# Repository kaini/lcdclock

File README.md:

# 7-Segment LCD Clock

Schematic, PCB and firmware (C++) for a 7-segment LCD clock. For details please
see [my site](https://me.pushrax.com/lcd-clock/).

## Build Instructions

Just use `make`. If you want a release build use `make RELEASE=1`. If you
have a SEGGER J-Link you can use `make flash` to flash the build output
onto a compatible microcontroller.

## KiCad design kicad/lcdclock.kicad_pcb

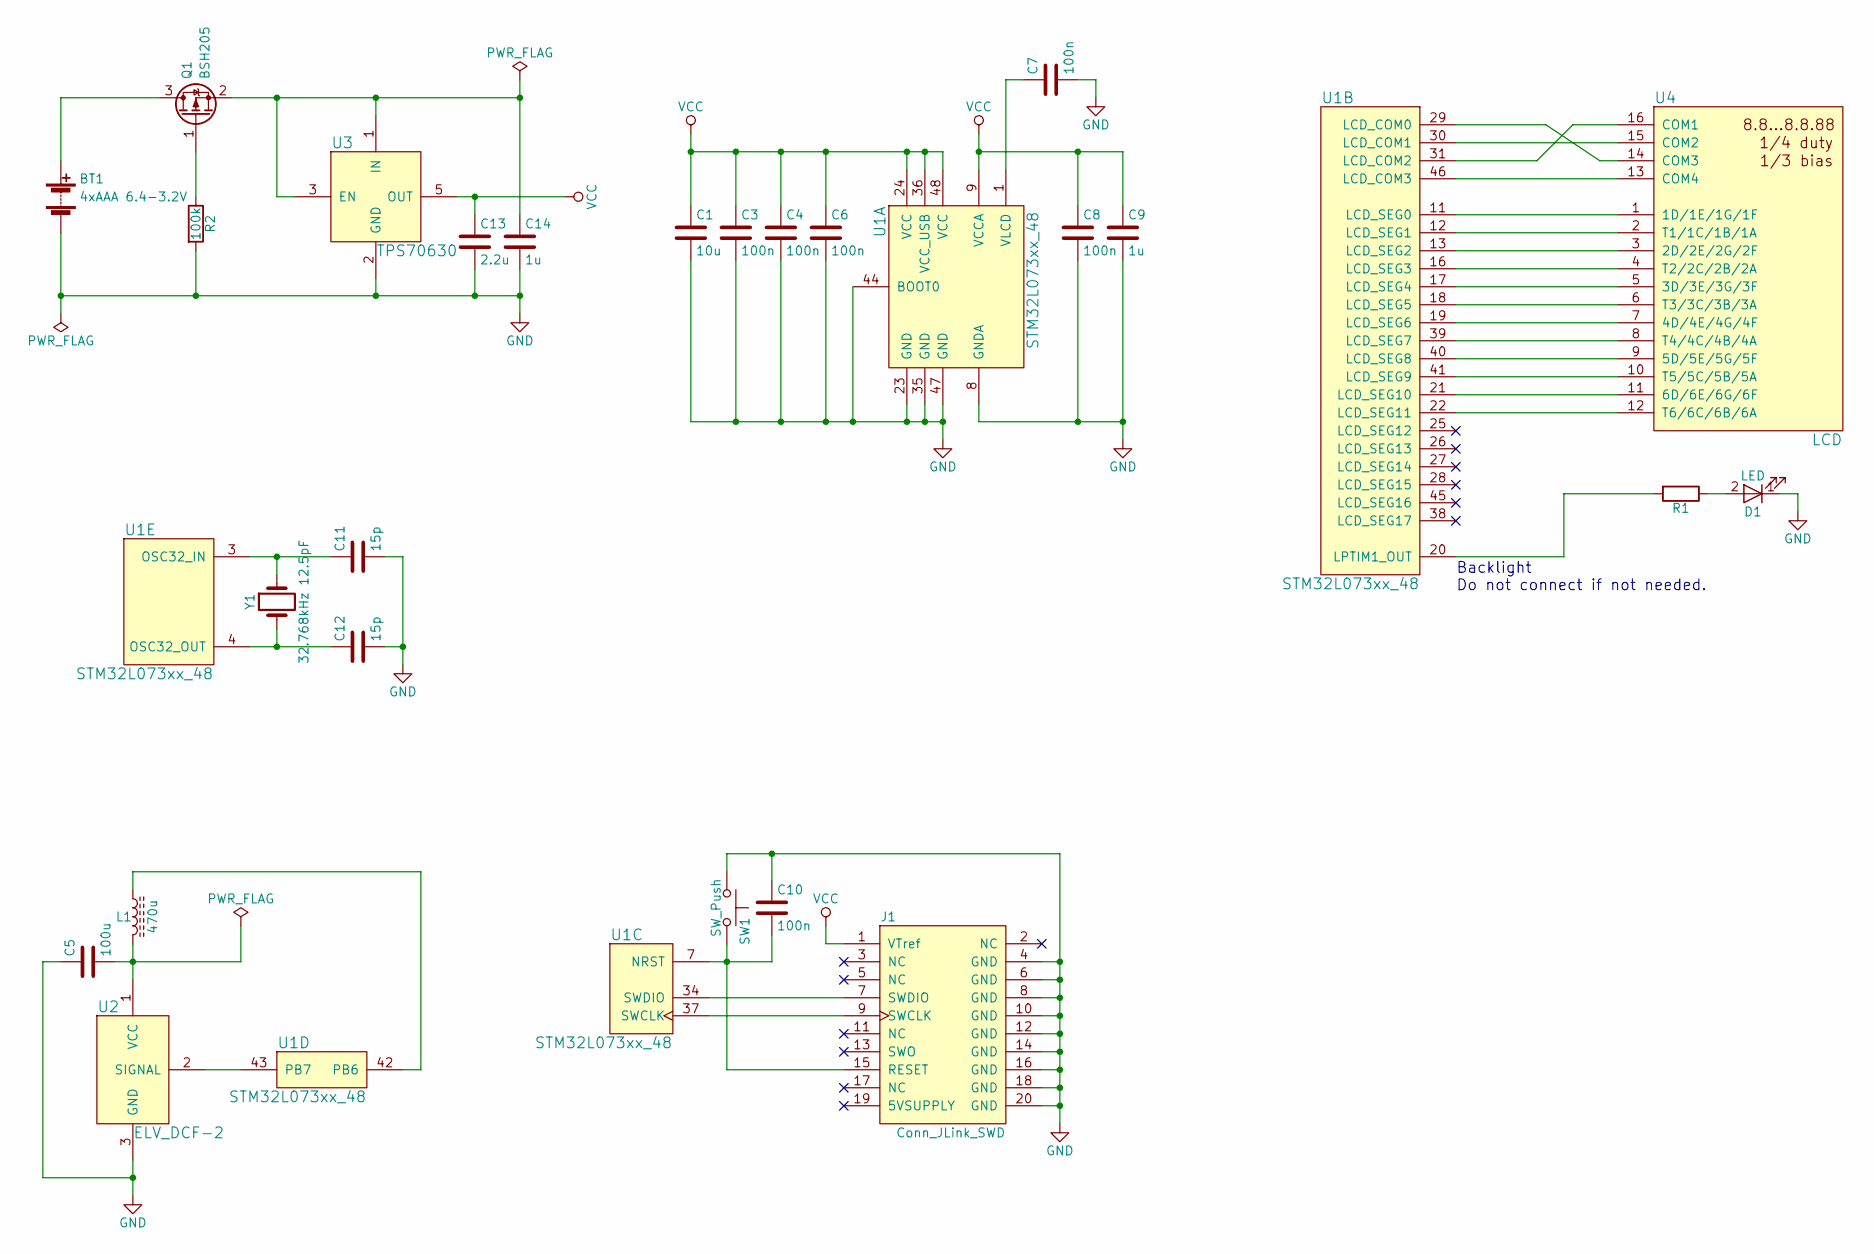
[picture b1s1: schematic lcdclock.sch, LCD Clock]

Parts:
BT1: 4xAAA 6.4-3.2V; CONNECTOR_2x1
C1: 10u; R_0805_HandSoldering
C3, C4, C6, C7, C8, C10: 100n; R_0805_HandSoldering
C5: 100u; R_1206_HandSoldering
C9, C14: 1u; R_0805_HandSoldering
C11, C12: 15p; R_0805_HandSoldering
C13: 2.2u; R_0805_HandSoldering
D1: LED; CONNECTOR_2x1
J1: Conn_JLink_SWD; IDC_Header_Straight_20pins
L1: 470u; R_1812_HandSoldering
Q1: BSH205; SOT-23_Handsoldering
R1: ?; R_0805_HandSoldering
R2: 100k; R_0805_HandSoldering
SW1: SW_Push; SW_SPST_B3S-1000
U1: STM32L073xx_48; LQFP-48_7x7mm_Pitch0.5mm
U2: ELV_DCF-2; CONNECTOR_3x1
U3: TPS70630; SOT-23-5_HandSoldering
U4: LCD; IDC_Header_Straight_16pins
Y1: 32.768kHz 12.5pF; Crystal_SMD_SeikoEpson_MC405-2pin_9.6x4.1mm

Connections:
GND: BT1.2 (-), C1.2, C3.2, C4.2, C5.1, C6.2, C7.2, C8.2, C9.2, C10.1, C11.2, C12.2, C13.2, C14.2, D1.1 (K), J1.4 (GND), J1.6 (GND), J1.8 (GND), J1.10 (GND), J1.12 (GND), J1.14 (GND), J1.16 (GND), J1.18 (GND), J1.20 (GND), R2.2, SW1.1, U1.8 (GNDA), U1.23 (GND), U1.35 (GND), U1.44 (BOOT0), U1.47 (GND), U2.3 (GND), U3.2 (GND)
unnamed: BT1.1 (+), Q1.3 (D)
unnamed: C5.2, L1.2, U2.1 (VCC)
unnamed: C7.1, U1.1 (VLCD)
unnamed: C10.2, J1.15 (RESET), SW1.2, U1.7 (NRST)
unnamed: C11.1, U1.3 (OSC32_IN), Y1.1
unnamed: C12.1, U1.4 (OSC32_OUT), Y1.2
unnamed: C14.1, Q1.2 (S), U3.1 (IN), U3.3 (EN)
unnamed: D1.2 (A), R1.1
unnamed: J1.7 (SWDIO), U1.34 (SWDIO)
unnamed: J1.9 (SWCLK), U1.37 (SWCLK)
unnamed: L1.1, U1.42 (PB6)
unnamed: Q1.1 (G), R2.1
unnamed: R1.2, U1.20 (LPTIM1_OUT)
unnamed: U1.11 (LCD_SEG0), U4.1 (1D/1E/1G/1F)
unnamed: U1.12 (LCD_SEG1), U4.2 (T1/1C/1B/1A)
unnamed: U1.13 (LCD_SEG2), U4.3 (2D/2E/2G/2F)
unnamed: U1.16 (LCD_SEG3), U4.4 (T2/2C/2B/2A)
unnamed: U1.17 (LCD_SEG4), U4.5 (3D/3E/3G/3F)
unnamed: U1.18 (LCD_SEG5), U4.6 (T3/3C/3B/3A)
unnamed: U1.19 (LCD_SEG6), U4.7 (4D/4E/4G/4F)
unnamed: U1.21 (LCD_SEG10), U4.11 (6D/6E/6G/6F)
unnamed: U1.22 (LCD_SEG11), U4.12 (T6/6C/6B/6A)
unnamed: U1.29 (LCD_COM0), U4.14 (COM3)
unnamed: U1.30 (LCD_COM1), U4.15 (COM2)
unnamed: U1.31 (LCD_COM2), U4.16 (COM1)
unnamed: U1.39 (LCD_SEG7), U4.8 (T4/4C/4B/4A)
unnamed: U1.40 (LCD_SEG8), U4.9 (5D/5E/5G/5F)
unnamed: U1.41 (LCD_SEG9), U4.10 (T5/5C/5B/5A)
unnamed: U1.43 (PB7), U2.2 (SIGNAL)
unnamed: U1.46 (LCD_COM3), U4.13 (COM4)
VCC: C1.1, C3.1, C4.1, C6.1, C8.1, C9.1, C13.1, J1.1 (VTref), U1.9 (VCCA), U1.24 (VCC), U1.36 (VCC_USB), U1.48 (VCC), U3.5 (OUT)

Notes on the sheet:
Backlight Do not connect if not needed.

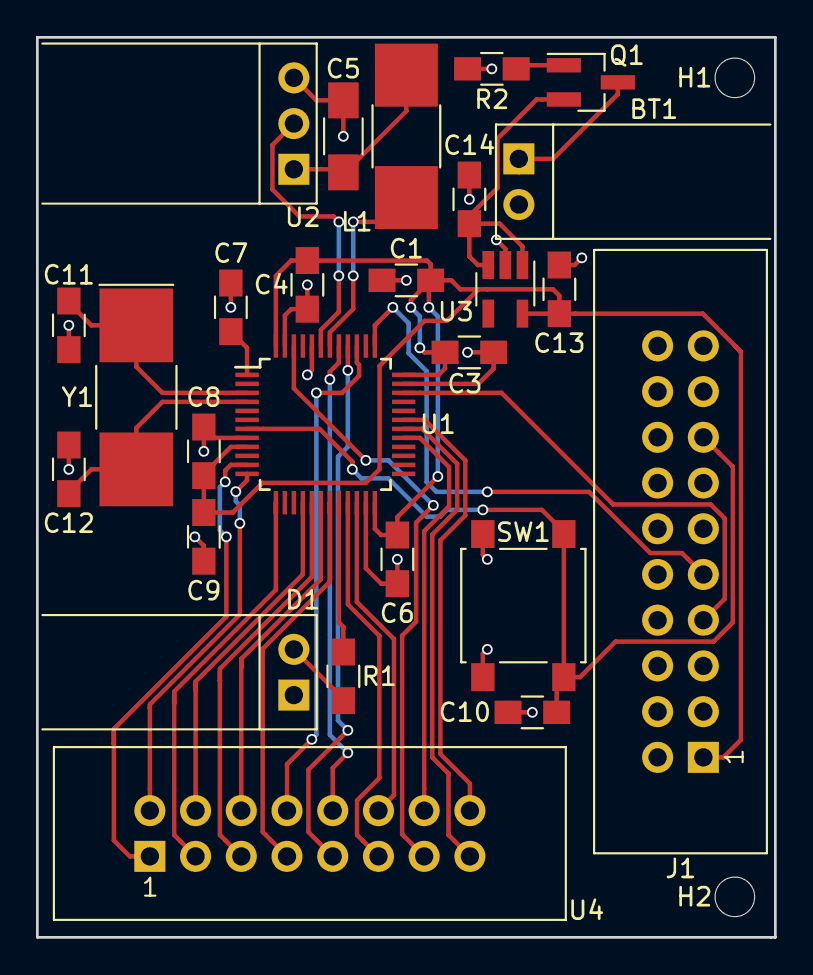
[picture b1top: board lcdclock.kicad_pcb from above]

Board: 2 copper layers, 41.0 x 50.0 mm, 28 parts (0 on the bottom side), 32 nets.

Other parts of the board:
H1, H2: MountingHole_2.2mm_M2

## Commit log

2017-09-15 Add schematic
2017-09-16 Route PCB
2017-09-18 Rework for a STM32 CPU
2017-09-19 Change LCD and CPU to 48 pins
2017-09-20 Select parts and assign footprints
2017-09-20 Place components on PCB
2017-09-20 Layout PCB
2017-09-20 Add two mounting holes
2017-09-21 Add reverse voltage protection
2017-09-25 Replace crystal Y1 footprint with a smaller one
2017-09-26 Working build
2017-09-28 Use newlib nano
2017-09-28 Do not seperate stack and heap
2017-09-29 Remove excessive track
2017-09-29 Unify drill sizes
2017-10-05 Implement stuff, yeah I need to commit more often
2017-10-06 Add support for tests
2017-10-07 Add -fno-strict-aliasing and -fshort-enums and fix .d-file issue
2017-10-07 Implement first DCF77 parser with tests
2017-10-07 Improve the second sync
2017-10-07 Make minute mark handling more flexible.
2017-10-07 Handle minute marks in data as unkowns
2017-10-07 Add CREDITS
2017-10-07 Assert refactoring and fix compiler warnings
2017-10-09 Make unsigned integer overflow defined
2017-10-16 First version that runs on the hardware
2017-10-18 Move some files to make the project IDE friendlier and make the LCD controller work
2017-10-20 Working DCF77, remove HAL
2017-10-22 First working version
2017-10-23 Replace semihosting with SEGGER RTT and add working main loop
2017-10-27 Do things with the date
2017-10-30 Temporary commit
2017-10-31 Refactor DCF77 parser and datetime to C++
2017-10-31 Put datetime into a namespace
2017-10-31 Fix code bloat, fix missing static constructors, fix interrupt race condition
2017-11-01 Port the display to C++
2017-11-02 Fix off by one error
2017-11-02 Add hardware comments
2017-11-02 Refactor the DCF77 module to a C++ class
2017-11-02 Add DST handling
2018-04-08 Add sleep and debugging touches
2018-04-08 Fix sleep modes
2018-04-17 Fixes & add case
2018-04-18 Less LCD segment ghosting
2018-04-21 Final fixes
2018-04-22 Add license and readme
2018-04-23 Fix two small issues in the PCB
